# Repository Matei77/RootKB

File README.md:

# RootKB - By Matei Ionescu

You can read about the project at: https://ocw.cs.pub.ro/courses/pm/prj2024/ccontasel/matei.ionescu0703

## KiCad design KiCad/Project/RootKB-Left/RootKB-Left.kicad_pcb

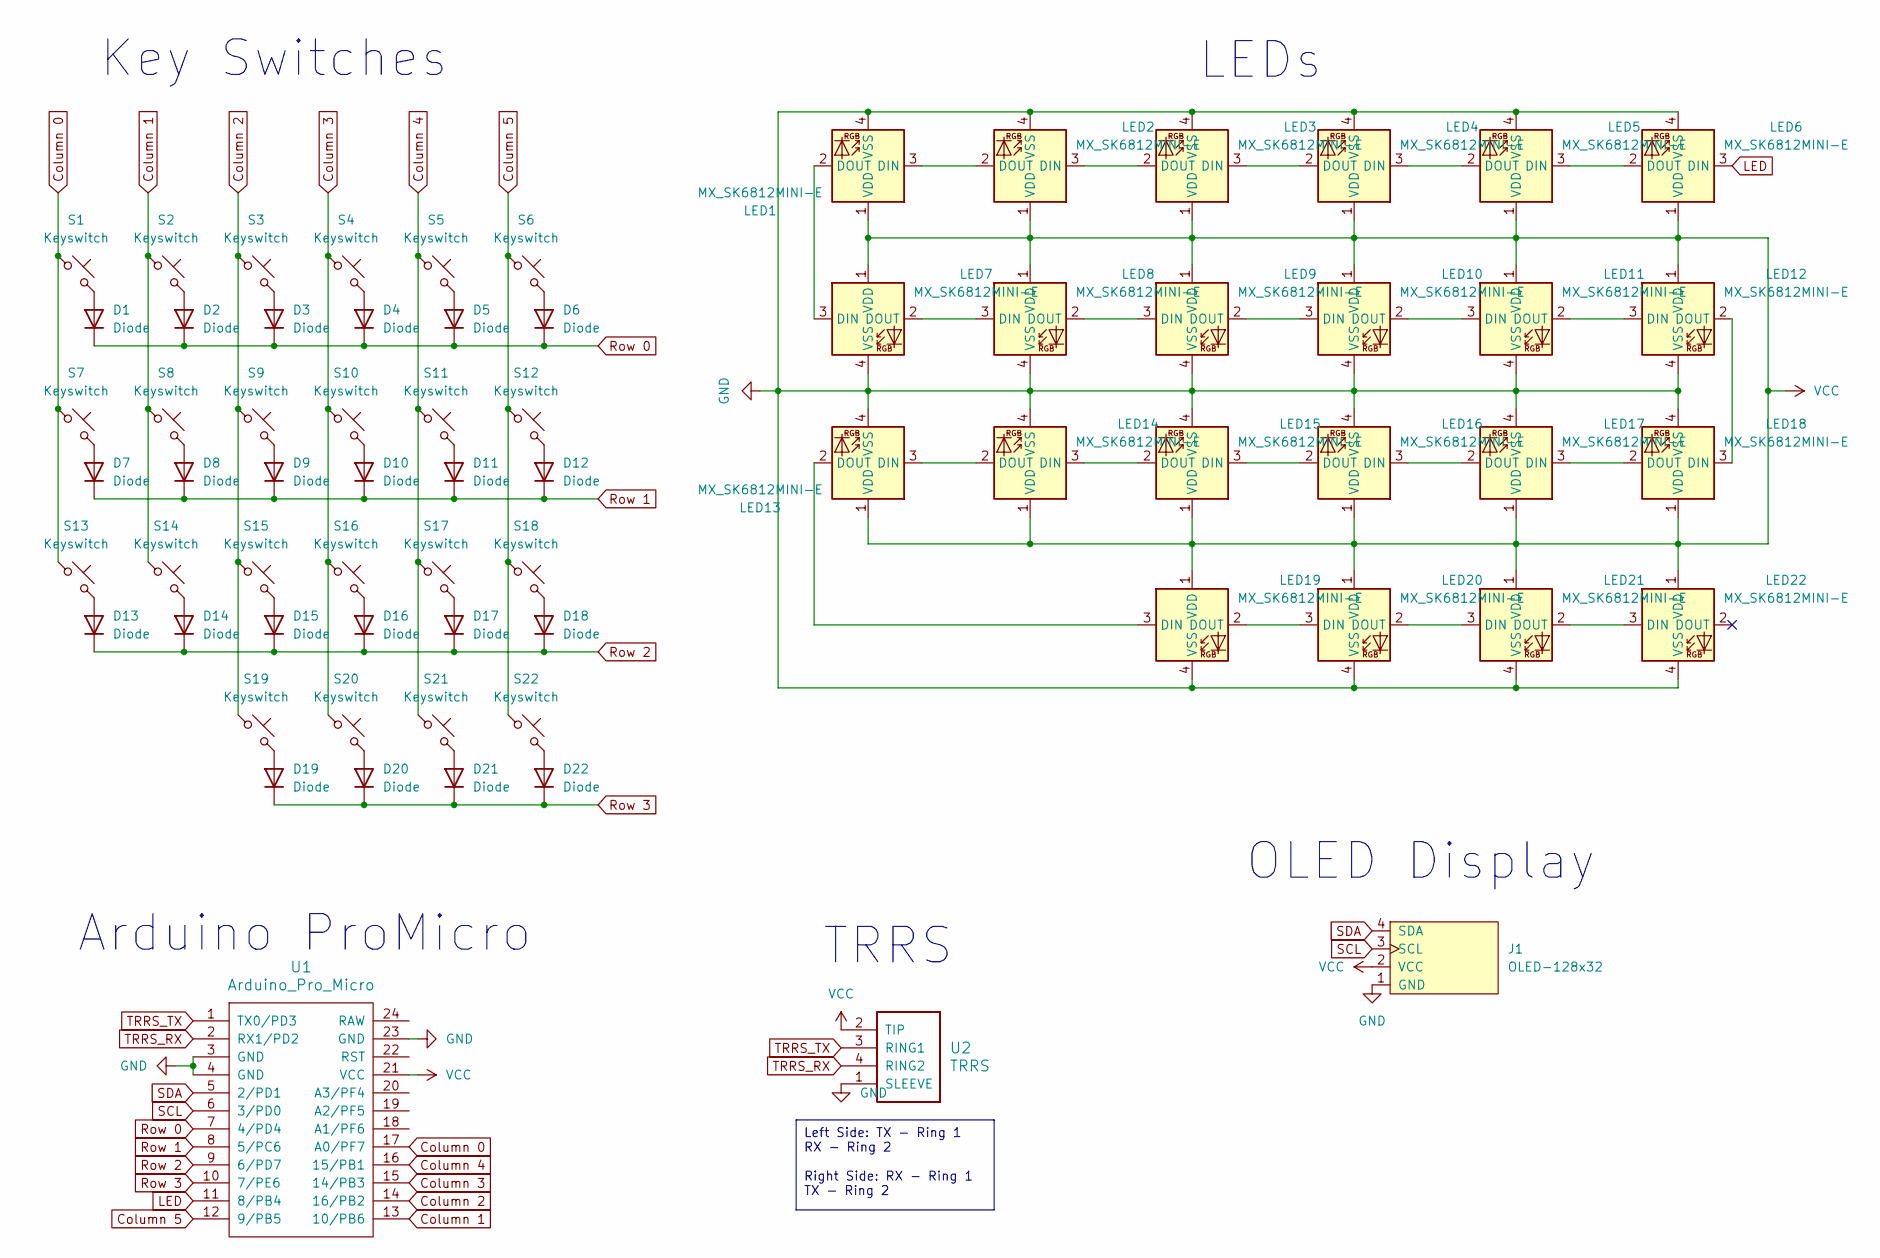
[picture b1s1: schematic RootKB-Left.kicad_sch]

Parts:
D1, D2, D3, D4, D5, D6, D7, D8, D9, D10, D11, D12, D13, D14, D15, D16, D17, D18, D19, D20, D21, D22: Diode; D_SOD-123F
J1: OLED-128x32; OLED-128x32-cutout
LED1, LED2, LED3, LED4, LED5, LED6, LED7, LED8, LED9, LED10, LED11, LED12, LED13, LED14, LED15, LED16, LED17, LED18, LED19, LED20, LED21, LED22: MX_SK6812MINI-E; LED_MX_6028R
S1, S2, S3, S4, S5, S6, S7, S8, S9, S10, S11, S12, S13, S14, S15, S16, S17, S18, S19, S22: Keyswitch; SW_Hotswap_Kailh_MX_1.00u
S20, S21: Keyswitch; SW_Hotswap_Kailh_MX_1.25u_90deg
U1: Arduino_Pro_Micro
U2: TRRS; TRRS_PJ-320A

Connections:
Column 0: S1.1, S7.1, S13.1, U1.17 (A0/PF7)
Column 1: S2.1, S8.1, S14.1, U1.13 (10/PB6)
Column 2: S3.1, S9.1, S15.1, S19.1, U1.14 (16/PB2)
Column 3: S4.1, S10.1, S16.1, S20.1, U1.15 (14/PB3)
Column 4: S5.1, S11.1, S17.1, S21.1, U1.16 (15/PB1)
Column 5: S6.1, S12.1, S18.1, S22.1, U1.12 (9/PB5)
GND: J1.1 (GND), LED1.4 (VSS), LED2.4 (VSS), LED3.4 (VSS), LED4.4 (VSS), LED5.4 (VSS), LED6.4 (VSS), LED7.4 (VSS), LED8.4 (VSS), LED9.4 (VSS), LED10.4 (VSS), LED11.4 (VSS), LED12.4 (VSS), LED13.4 (VSS), LED14.4 (VSS), LED15.4 (VSS), LED16.4 (VSS), LED17.4 (VSS), LED18.4 (VSS), LED19.4 (VSS), LED20.4 (VSS), LED21.4 (VSS), LED22.4 (VSS), U1.3 (GND), U1.4 (GND), U1.23 (GND), U2.1 (SLEEVE)
LED: LED6.3 (DIN), U1.11 (8/PB4)
unnamed: D1.2 (A), S1.2
unnamed: D2.2 (A), S2.2
unnamed: D3.2 (A), S3.2
unnamed: D4.2 (A), S4.2
unnamed: D5.2 (A), S5.2
unnamed: D6.2 (A), S6.2
unnamed: D7.2 (A), S7.2
unnamed: D8.2 (A), S8.2
unnamed: D9.2 (A), S9.2
unnamed: D10.2 (A), S10.2
unnamed: D11.2 (A), S11.2
unnamed: D12.2 (A), S12.2
unnamed: D13.2 (A), S13.2
unnamed: D14.2 (A), S14.2
unnamed: D15.2 (A), S15.2
unnamed: D16.2 (A), S16.2
unnamed: D17.2 (A), S17.2
unnamed: D18.2 (A), S18.2
unnamed: D19.2 (A), S19.2
unnamed: D20.2 (A), S20.2
unnamed: D21.2 (A), S21.2
unnamed: D22.2 (A), S22.2
unnamed: LED1.3 (DIN), LED2.2 (DOUT)
unnamed: LED1.2 (DOUT), LED7.3 (DIN)
unnamed: LED2.3 (DIN), LED3.2 (DOUT)
unnamed: LED3.3 (DIN), LED4.2 (DOUT)
unnamed: LED4.3 (DIN), LED5.2 (DOUT)
unnamed: LED5.3 (DIN), LED6.2 (DOUT)
unnamed: LED7.2 (DOUT), LED8.3 (DIN)
unnamed: LED8.2 (DOUT), LED9.3 (DIN)
unnamed: LED9.2 (DOUT), LED10.3 (DIN)
unnamed: LED10.2 (DOUT), LED11.3 (DIN)
unnamed: LED11.2 (DOUT), LED12.3 (DIN)
unnamed: LED12.2 (DOUT), LED18.3 (DIN)
unnamed: LED13.3 (DIN), LED14.2 (DOUT)
unnamed: LED13.2 (DOUT), LED19.3 (DIN)
unnamed: LED14.3 (DIN), LED15.2 (DOUT)
unnamed: LED15.3 (DIN), LED16.2 (DOUT)
unnamed: LED16.3 (DIN), LED17.2 (DOUT)
unnamed: LED17.3 (DIN), LED18.2 (DOUT)
unnamed: LED19.2 (DOUT), LED20.3 (DIN)
unnamed: LED20.2 (DOUT), LED21.3 (DIN)
unnamed: LED21.2 (DOUT), LED22.3 (DIN)
Row 0: D1.1 (K), D2.1 (K), D3.1 (K), D4.1 (K), D5.1 (K), D6.1 (K), U1.7 (4/PD4)
Row 1: D7.1 (K), D8.1 (K), D9.1 (K), D10.1 (K), D11.1 (K), D12.1 (K), U1.8 (5/PC6)
Row 2: D13.1 (K), D14.1 (K), D15.1 (K), D16.1 (K), D17.1 (K), D18.1 (K), U1.9 (6/PD7)
Row 3: D19.1 (K), D20.1 (K), D21.1 (K), D22.1 (K), U1.10 (7/PE6)
SCL: J1.3 (SCL), U1.6 (3/PD0)
SDA: J1.4 (SDA), U1.5 (2/PD1)
TRRS_RX: U1.2 (RX1/PD2), U2.4 (RING2)
TRRS_TX: U1.1 (TX0/PD3), U2.3 (RING1)
VCC: J1.2 (VCC), LED1.1 (VDD), LED2.1 (VDD), LED3.1 (VDD), LED4.1 (VDD), LED5.1 (VDD), LED6.1 (VDD), LED7.1 (VDD), LED8.1 (VDD), LED9.1 (VDD), LED10.1 (VDD), LED11.1 (VDD), LED12.1 (VDD), LED13.1 (VDD), LED14.1 (VDD), LED15.1 (VDD), LED16.1 (VDD), LED17.1 (VDD), LED18.1 (VDD), LED19.1 (VDD), LED20.1 (VDD), LED21.1 (VDD), LED22.1 (VDD), U1.21 (VCC), U2.2 (TIP)

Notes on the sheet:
Left Side: TX - Ring 1 RX - Ring 2 Right Side: RX - Ring 1 TX - Ring 2
Arduino ProMicro
TRRS
LEDs
Key Switches
OLED Display

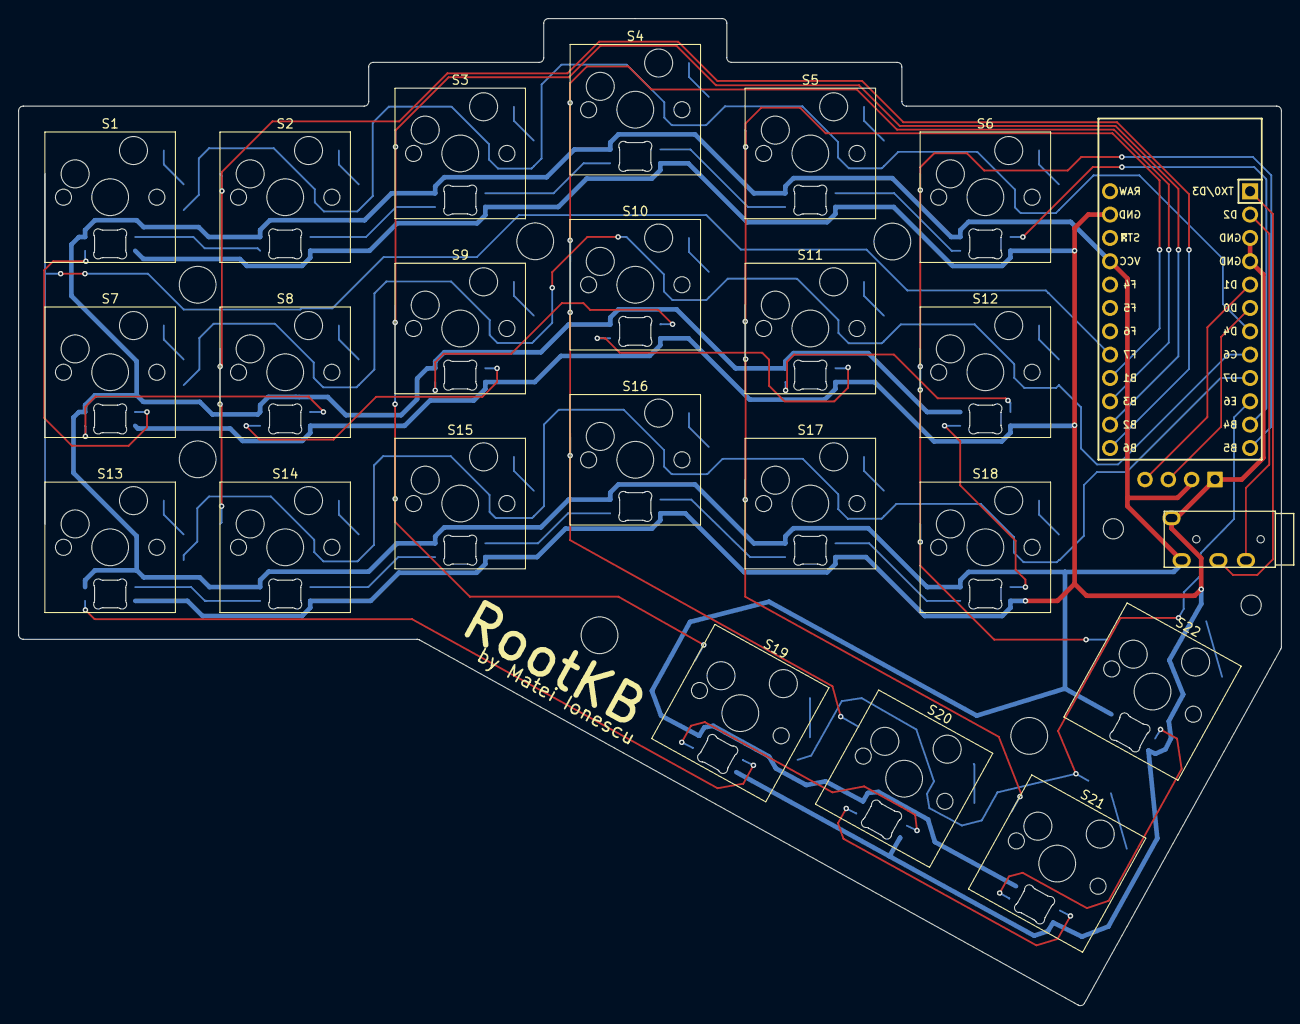
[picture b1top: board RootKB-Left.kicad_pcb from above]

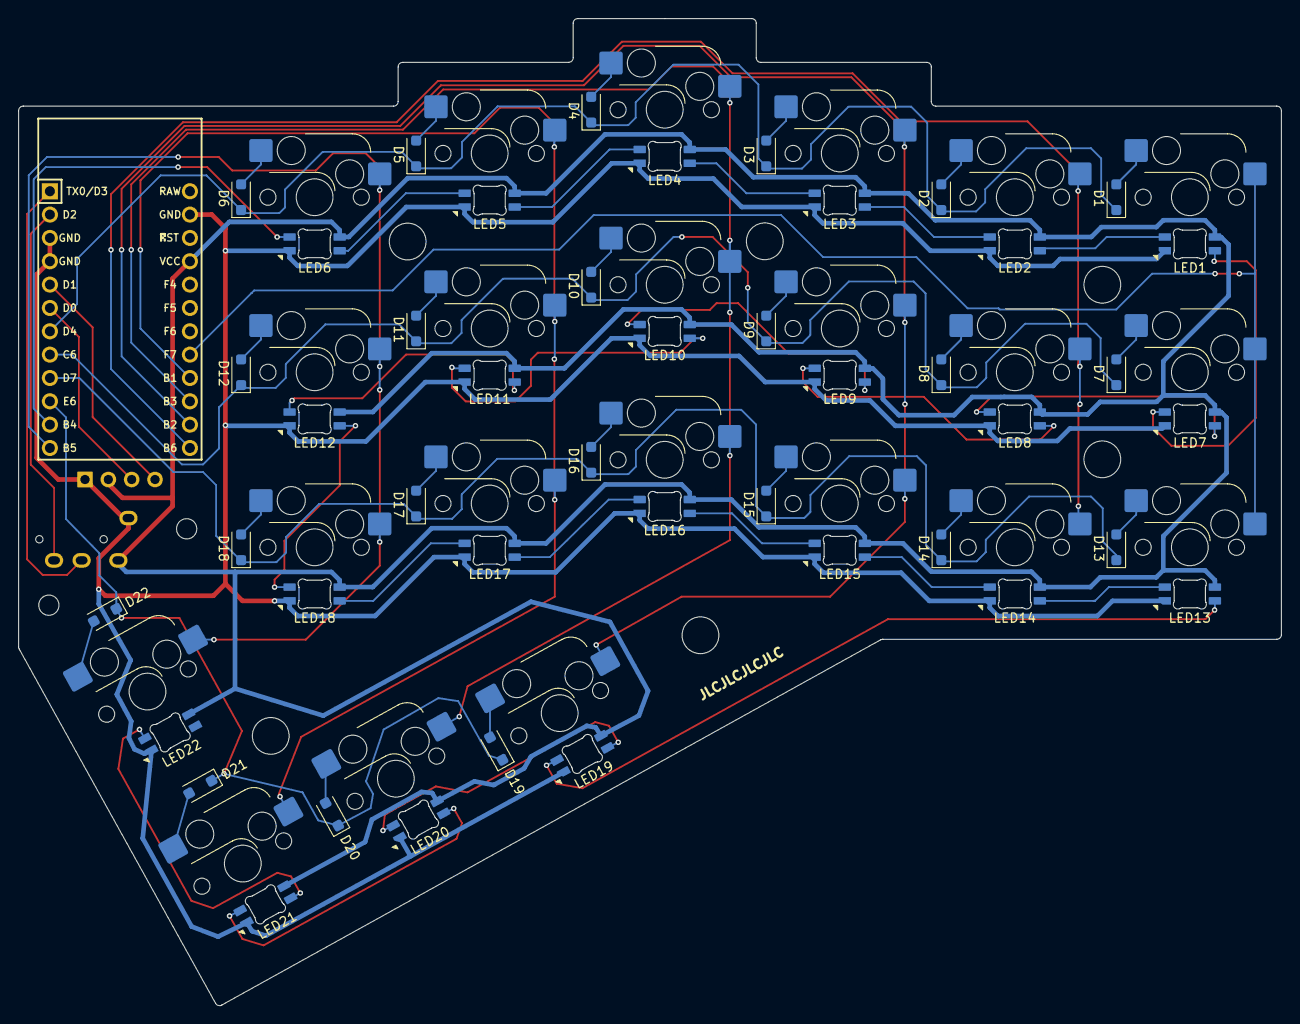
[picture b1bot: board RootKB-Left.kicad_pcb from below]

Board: 2 copper layers, 137.4 x 107.4 mm, 69 parts (45 on the bottom side), 60 nets.

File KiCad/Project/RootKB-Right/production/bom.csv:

Designator,Footprint,Quantity,Value,LCSC Part #
"D1, D10, D11, D12, D13, D14, D15, D16, D17, D18, D19, D2, D20, D21, D22, D3, D4, D5, D6, D7, D8, D9",D_SOD-123F,22,Diode,
"LED1, LED10, LED11, LED12, LED13, LED14, LED15, LED16, LED17, LED18, LED19, LED2, LED20, LED21, LED22, LED3, LED4, LED5, LED6, LED7, LED8, LED9",LED_MX_6028R,22,MX_SK6812MINI-E,
"S1, S10, S11, S12, S13, S14, S15, S16, S17, S18, S19, S2, S22, S3, S4, S5, S6, S7, S8, S9",SW_Hotswap_Kailh_MX_1.00u,20,Keyswitch,
"S20, S21",SW_Hotswap_Kailh_MX_1.25u_90deg,2,Keyswitch,
U1,Arduino_Pro_Micro,1,Arduino_Pro_Micro,
U2,TRRS_PJ-320A,1,TRRS,

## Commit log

2024-04-26 add Ergogen design
2024-04-26 add KiCad project
2024-04-27 update pcb
2024-04-27 move screen cover holes
2024-04-27 adjust for larger arduino pro micro (Type C)
2024-04-27 add right side
2024-04-27 update pro micro silkscreen
2024-04-28 route left
2024-05-02 routing left
2024-05-02 remove reset button
    also use real Arduino ProMicro dimensions
2024-05-02 fix track
2024-05-02 move vias away from pads
2024-05-02 update ProMicro silkscreen
2024-05-04 add docs
2024-05-04 add outlines
2024-05-04 add component libraries used
2024-05-04 add pro micro measurements
2024-05-04 add jblpcb order number location
2024-05-05 use UART
2024-05-05 Make symmetrical right PCB
2024-05-05 add titles
2024-05-05 route tracks on right side
2024-05-05 update routes
    more clearance for some routes
2024-05-07 minor routing changes
2024-05-08 update routing
2024-05-08 last updates
2024-05-08 add production files
2024-05-11 restructure project
2024-05-11 add plate files
2024-05-12 add casing
2024-05-12 add hardware images
2024-05-12 fix ergogen padding
2024-05-19 add keyboard characters layout
2024-05-19 add software for left side
2024-05-19 add software for right side
2024-05-19 send keys from multiple layers
2024-05-19 lower delay
2024-05-19 use rgb and oled on both halves
2024-05-27 keyboard light control
2024-05-27 display info on screen
2024-05-27 add function keys and PrtSc
2024-05-27 add special characters
2024-05-27 Create LICENSE
2024-05-27 update docs
2024-05-27 remove safety button
2025-06-03 fix repeating keys
2025-06-03 debounce key presses
2025-06-04 fixed syncronization issues
2025-06-11 get layout from app
2025-06-12 request matrix from the other half to avoid sync issues + create rgb modes
2025-06-12 fix sync issues on rgb mode change
2025-06-12 save rgb in eeprom
2025-06-12 lower rainbow effect speed
2025-06-12 save layout to eeprom
2025-06-13 use eeprom update instead of write
2025-06-13 refactor code
2025-06-13 tidycode right half
2025-06-14 app communication interface
2025-06-14 add more rgb effects
2025-06-15 serial read more than buffer size
